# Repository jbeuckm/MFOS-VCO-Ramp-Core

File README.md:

# MFOS-VCO-Ramp-Core
one-sided PCB layout for Ray's most up to date VCO core (includes ramp output)

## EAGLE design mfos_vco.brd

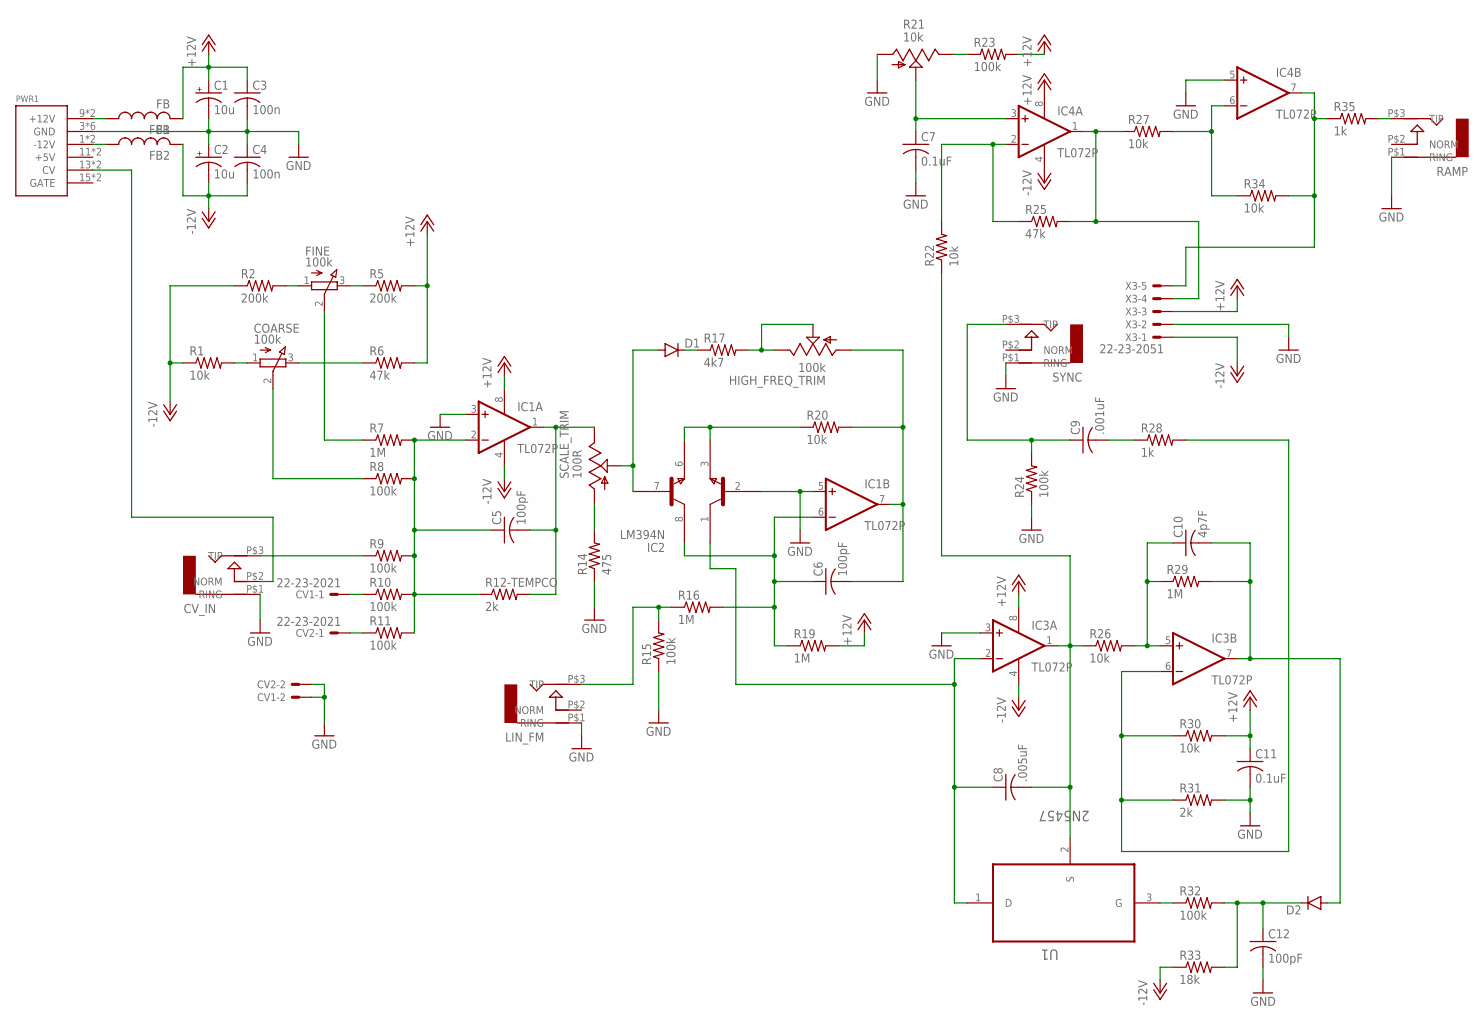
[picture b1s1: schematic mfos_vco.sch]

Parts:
C1, C2: 10u; B45181A
C3, C4: 100n; C050-024X044
C5, C6, C12: 100pF; C050-024X044
C7, C11: 0.1uF; C050-024X044
C8: .005uF; C050-024X044
C9: .001uF; C050-024X044
C10: 4p7F; C050-024X044
COARSE: 100k; 3RP/1610N
CV1, CV2: 22-23-2021
CV_IN: AUDIO-JACK; ERTHENVAR-JACK-90DEG
D1, D2: DIODE1N4148; DIODE-1N4148
FB1, FB2: FB
FINE: 100k; 3RP/1610N
HIGH_FREQ_TRIM: 100k; B64Y
IC1, IC3, IC4: TL072P; DIL08
IC2: LM394N; DIL08
LIN_FM: AUDIO-JACK; ERTHENVAR-JACK-90DEG
PWR1: POWER; POWER_16
R1, R20, R22, R26, R27, R30, R34: 10k; 0207/7
R2, R5: 200k; 0207/7
R6, R25: 47k; 0207/7
R7, R16, R19, R29: 1M; 0207/7
R8, R9, R10, R11, R15, R24, R32: 100k; 0207/7
R12-TEMPCO: 2k; 0207/2V
R14: 475; 0207/7
R17: 4k7; 0207/7
R21: 10k; B64Y
R23: 100k; 0207/10
R28, R35: 1k; 0207/7
R31: 2k; 0207/7
R33: 18k; 0207/7
RAMP: AUDIO-JACK; ERTHENVAR-JACK-90DEG
SCALE_TRIM: 100R; B64Y
SYNC: AUDIO-JACK; ERTHENVAR-JACK-90DEG
U1: 2N5457; TO127P254X732-3
X3: 22-23-2051

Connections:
+12V: C1.+, C3.1, C11.1, FB1.P$2 (2), IC1.8 (V+), IC3.8 (V+), IC4.8 (V+), R5.2, R6.2, R19.2, R23.2, R30.2, X3.3
-12V: C2.-, C4.2, FB2.P$2 (2), IC1.4 (V-), IC3.4 (V-), IC4.4 (V-), R1.1, R2.1, R33.1, X3.1
GND: C1.-, C2.+, C3.2, C4.1, C7.2, C11.2, C12.2, CV1.2, CV2.2, CV_IN.P$1 (RING), IC1.3 (+IN), IC1.5 (+IN), IC2.2 (B1), IC3.3 (+IN), IC4.5 (+IN), LIN_FM.P$1 (RING), PWR1.3 (GND), PWR1.4 (GND), PWR1.5 (GND), PWR1.6 (GND), PWR1.7 (GND), PWR1.8 (GND), R14.1, R15.1, R21.A, R24.1, R31.2, RAMP.P$1 (RING), SYNC.P$1 (RING), X3.2
unnamed: COARSE.1 (A), R1.2
unnamed: FINE.1 (A), R2.2
unnamed: FINE.3 (E), R5.1
unnamed: COARSE.3 (E), R6.1
unnamed: FINE.2 (S), R7.1
unnamed: COARSE.2 (S), R8.1
unnamed: R14.2, SCALE_TRIM.A
unnamed: D1.A, IC2.7 (B2), SCALE_TRIM.S
unnamed: C5.2, IC1.1 (OUT), R12-TEMPCO.2, SCALE_TRIM.E
unnamed: C5.1, IC1.2 (-IN), R7.2, R8.2, R9.2, R10.2, R11.2, R12-TEMPCO.1
unnamed: CV_IN.P$2 (NORM), PWR1.13 (CV), PWR1.14 (CV)
unnamed: IC2.3 (E1), IC2.6 (E2), R20.1
unnamed: HIGH_FREQ_TRIM.E, HIGH_FREQ_TRIM.S, R17.2
unnamed: D1.C, R17.1
unnamed: C6.2, HIGH_FREQ_TRIM.A, IC1.7 (OUT), R20.2
unnamed: CV_IN.P$3 (TIP), R9.1
unnamed: CV1.1, R10.1
unnamed: CV2.1, R11.1
unnamed: LIN_FM.P$3 (TIP), R15.2, R16.1
unnamed: C8.2, IC3.1 (OUT), R22.1, R26.1, U1.2 (S)
unnamed: C10.1, IC3.5 (+IN), R26.2, R29.1
unnamed: C8.1, IC2.1 (C1), IC3.2 (-IN), U1.1 (D)
unnamed: C9.2, R28.1
unnamed: C9.1, R24.2, SYNC.P$3 (TIP)
unnamed: IC3.6 (-IN), R28.2, R30.1, R31.1
unnamed: R21.E, R23.1
unnamed: C7.1, IC4.3 (+IN), R21.S
unnamed: R32.1, U1.3 (G)
unnamed: C10.2, D2.A, IC3.7 (OUT), R29.2
unnamed: IC4.2 (-IN), R22.2, R25.1
unnamed: C12.1, D2.C, R32.2, R33.2
unnamed: IC4.1 (OUT), R25.2, R27.1, X3.4
unnamed: IC4.6 (-IN), R27.2, R34.1
unnamed: IC4.7 (OUT), R34.2, R35.1, X3.5
unnamed: R35.2, RAMP.P$3 (TIP)
unnamed: FB1.P$1 (1), PWR1.9 (+12V), PWR1.10 (+12V)
unnamed: FB2.P$1 (1), PWR1.1 (-12V), PWR1.2 (-12V)
unnamed: C6.1, IC1.6 (-IN), IC2.8 (C2), R16.2, R19.1

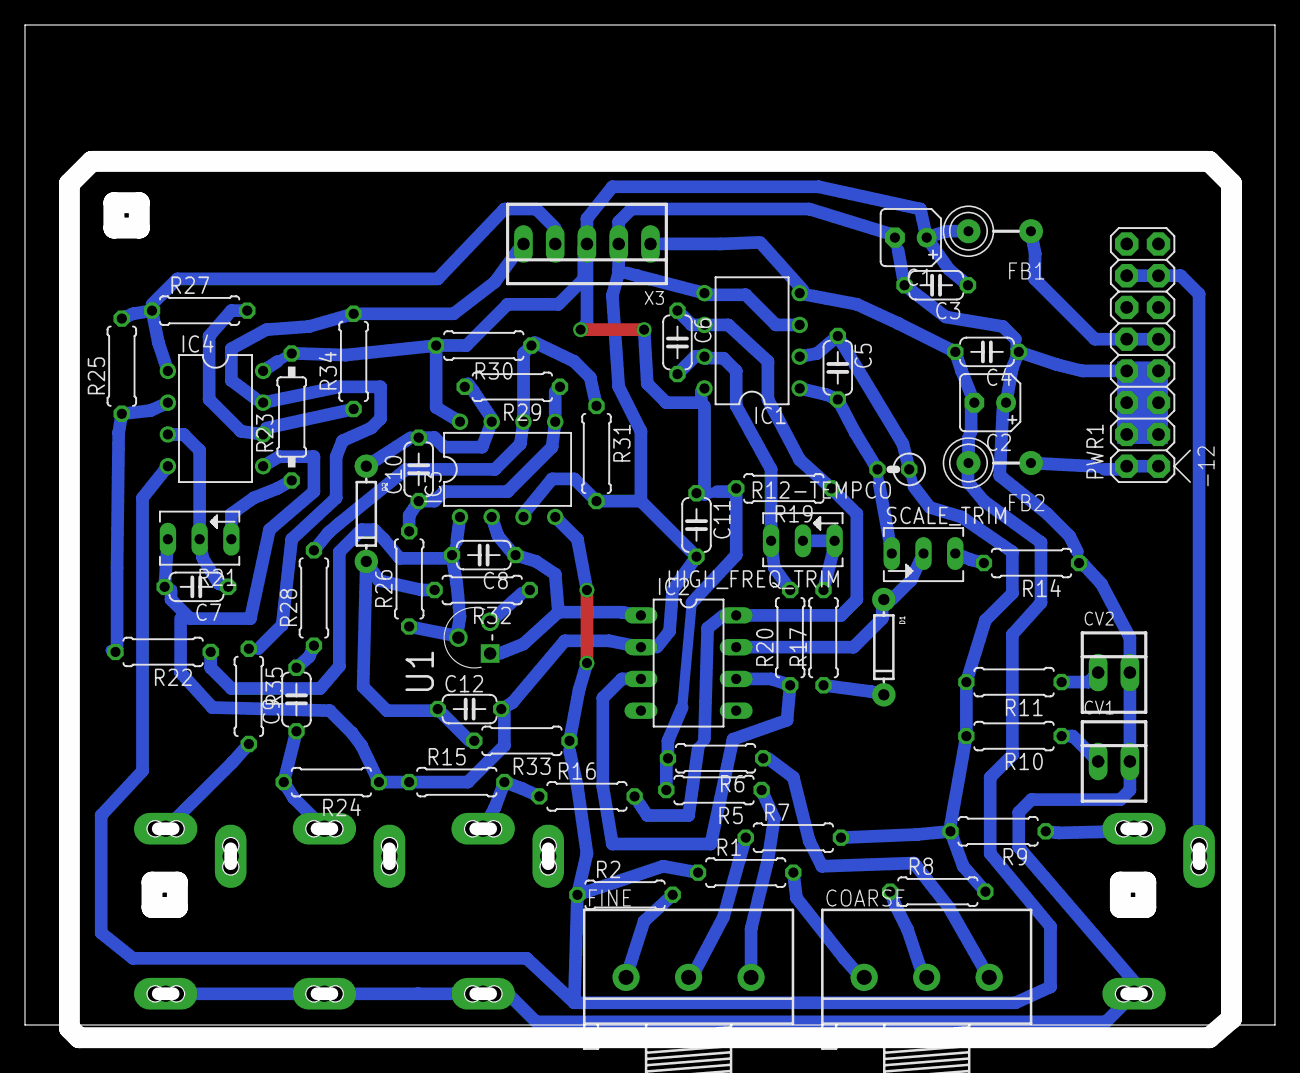
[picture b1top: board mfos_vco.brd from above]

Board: 2 copper layers, 100.0 x 81.0 mm, 64 parts (0 on the bottom side), 41 nets.

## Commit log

2015-09-11 ready to test cut the core...
2015-09-18 same problem
2015-09-19 changed to mpf102 device to ensure pinout
2015-09-29 ready to try lm394
2015-10-02 core works again with header for ribbon to shaper board
2015-12-14 thicker traces and fewer jumps
2015-12-14 layout image
2016-03-17 molex
2016-03-25 corrected separate ground signals and manually routed
2016-03-25 routed manually with two jumpers
2016-03-25 thicker traces
2016-03-25 cutout and thicker traces
2016-03-25 moved negative trace away from front panel edge
2016-03-25 tweaked traces
2017-04-20 pdf mirrored to fix the reverse

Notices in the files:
parts and their libraries:
SparkFun-DiscreteSemi: Licensing: Creative Commons ShareAlike 4.0 International - https://creativecommons.org/licenses/by-sa/4.0
